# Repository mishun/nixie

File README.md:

Simple Nixe Clock
=================

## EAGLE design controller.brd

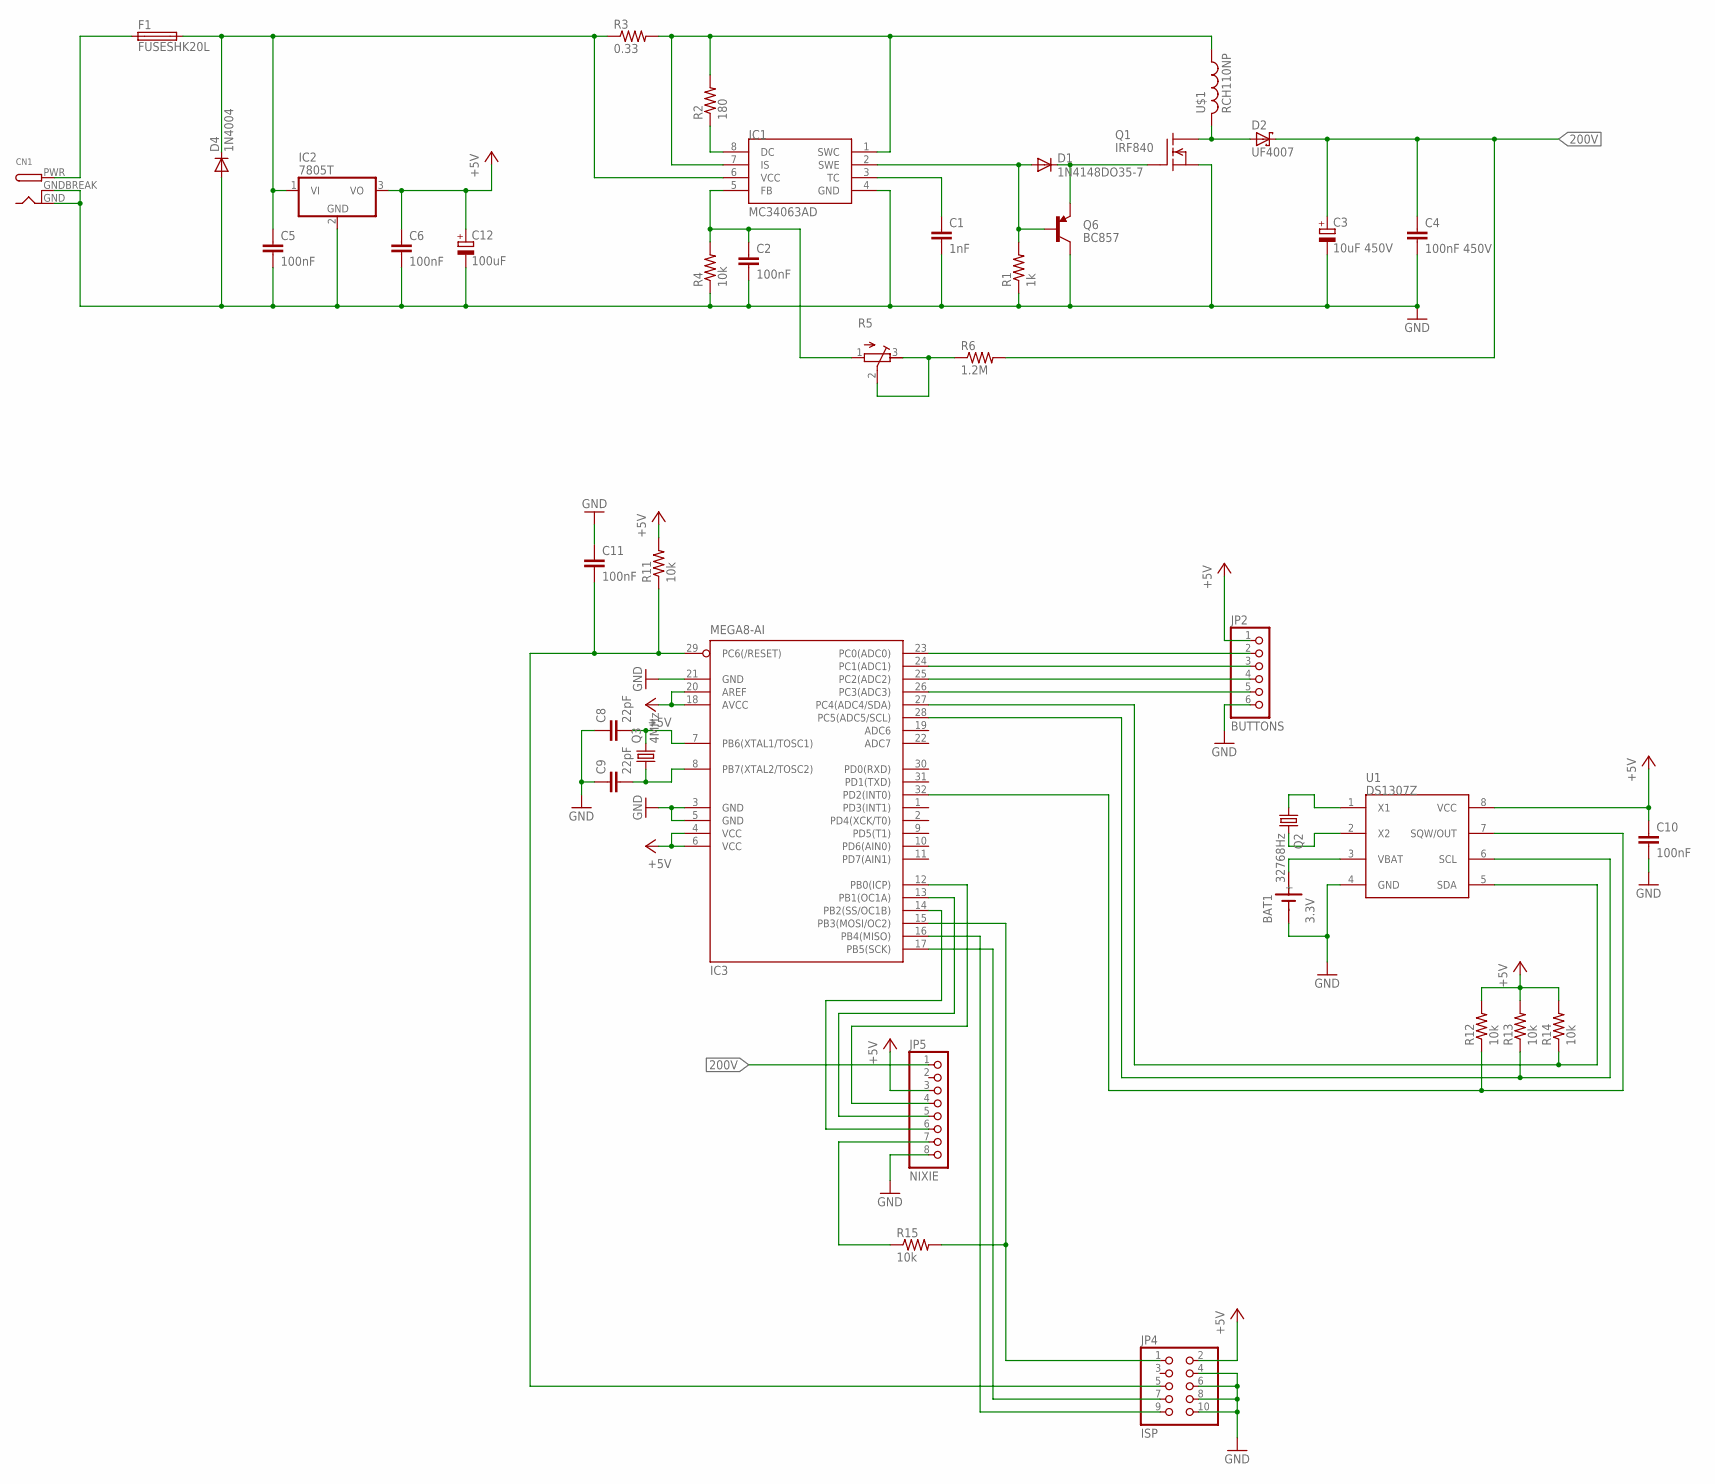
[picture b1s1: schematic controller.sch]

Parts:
BAT1: 3.3V; SN2032
C1: 1nF; 0805
C2, C5, C6, C10, C11: 100nF; 0805
C3: 10uF 450V; E5-13
C4: 100nF 450V; CAP-PTH-LARGE
C8, C9: 22pF; 0805
C12: 100uF; E3,5-8
CN1: DCBARRELPTH; DCJACK_2MM_PTH
D1: 1N4148DO35-7; DO35-7
D2: UF4007; DO41-7.6
D4: 1N4004; DO41-10
F1: FUSESHK20L; SHK20L
IC1: MC34063AD; SOIC8
IC2: 7805T; TO220H
IC3: MEGA8-AI; TQFP32-08
JP2: BUTTONS; 1X06/90
JP4: ISP; 2X05/90
JP5: NIXIE; 1X08
Q1: IRF840; TO220
Q2: 32768Hz; TC38H
Q3: 4MHz; HC49U-V
Q6: BC857; SOT23-3
R1: 1k; 0805
R2: 180; 0805
R3: 0.33; AXIAL-0.8
R4, R11, R12, R13, R14, R15: 10k; 0805
R5: R-TRIMM64Z; RTRIM64Z
R6: 1.2M; AXIAL-0.8
U1: DS1307Z; SOIC8
U$1: RCH110NP

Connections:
200V: C3.+, C4.1, D2.C, JP5.1, R6.P$2 (2)
+5V: C6.1, C10.1, C12.+, IC2.3 (VO), IC3.4 (VCC), IC3.6 (VCC), IC3.18 (AVCC), IC3.20 (AREF), JP2.1, JP4.2, JP5.3, R11.2, R12.2, R13.2, R14.2, U1.8 (VCC)
GND: BAT1.-, C1.2, C2.2, C3.-, C4.2, C5.2, C6.2, C8.1, C9.1, C10.2, C11.1, C12.-, CN1.GND, CN1.GNDBREAK, D4.A, IC1.4 (GND), IC2.2 (GND), IC3.3 (GND), IC3.5 (GND), IC3.21 (GND), JP2.6, JP4.4, JP4.6, JP4.8, JP4.10, JP5.8, Q1.3 (S), Q6.3 (C), R1.1, R4.1, U1.4 (GND)
unnamed: D1.C, Q1.1 (G), Q6.2 (E)
unnamed: D1.A, IC1.2 (SWE), Q6.1 (B), R1.2
unnamed: IC3.23 (PC0(ADC0)), JP2.2
unnamed: D2.A, Q1.2 (D), U$1.B (2)
unnamed: C1.1, IC1.3 (TC)
unnamed: IC1.8 (DC), R2.1
unnamed: IC1.1 (SWC), IC1.7 (IS), R2.2, R3.P$2 (2), U$1.A (1)
unnamed: C5.1, D4.C, F1.2A (2), IC1.6 (VCC), IC2.1 (VI), R3.P$1 (1)
unnamed: C11.2, IC3.29 (PC6(/RESET)), JP4.5, R11.1
unnamed: C2.1, IC1.5 (FB), R4.2, R5.1 (A)
unnamed: R5.2 (S), R5.3 (E), R6.P$1 (1)
unnamed: IC3.27 (PC4(ADC4/SDA)), R14.1, U1.5 (SDA)
unnamed: IC3.24 (PC1(ADC1)), JP2.3
unnamed: IC3.25 (PC2(ADC2)), JP2.4
unnamed: IC3.26 (PC3(ADC3)), JP2.5
unnamed: IC3.28 (PC5(ADC5/SCL)), R13.1, U1.6 (SCL)
unnamed: IC3.32 (PD2(INT0)), R12.1, U1.7 (SQW/OUT)
unnamed: IC3.15 (PB3(MOSI/OC2)), JP4.1, R15.2
unnamed: IC3.17 (PB5(SCK)), JP4.7
unnamed: IC3.16 (PB4(MISO)), JP4.9
unnamed: BAT1.+, U1.3 (VBAT)
unnamed: IC3.12 (PB0(ICP)), JP5.4
unnamed: Q2.1, U1.1 (X1)
unnamed: Q2.2, U1.2 (X2)
unnamed: C8.2, IC3.7 (PB6(XTAL1/TOSC1)), Q3.2
unnamed: C9.2, IC3.8 (PB7(XTAL2/TOSC2)), Q3.1
unnamed: CN1.PWR, F1.1A (1)
unnamed: IC3.13 (PB1(OC1A)), JP5.5
unnamed: IC3.14 (PB2(SS/OC1B)), JP5.6
unnamed: JP5.7, R15.1

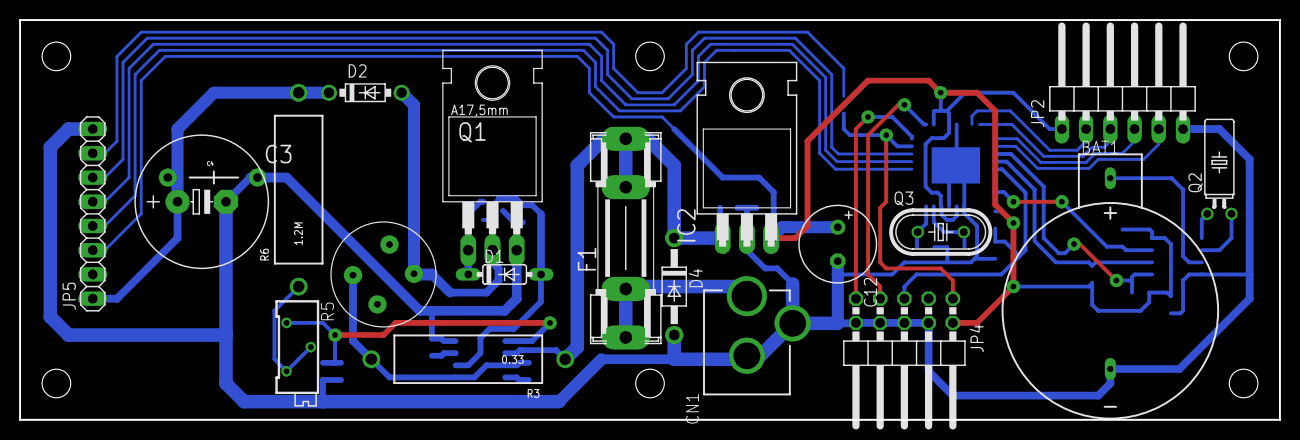
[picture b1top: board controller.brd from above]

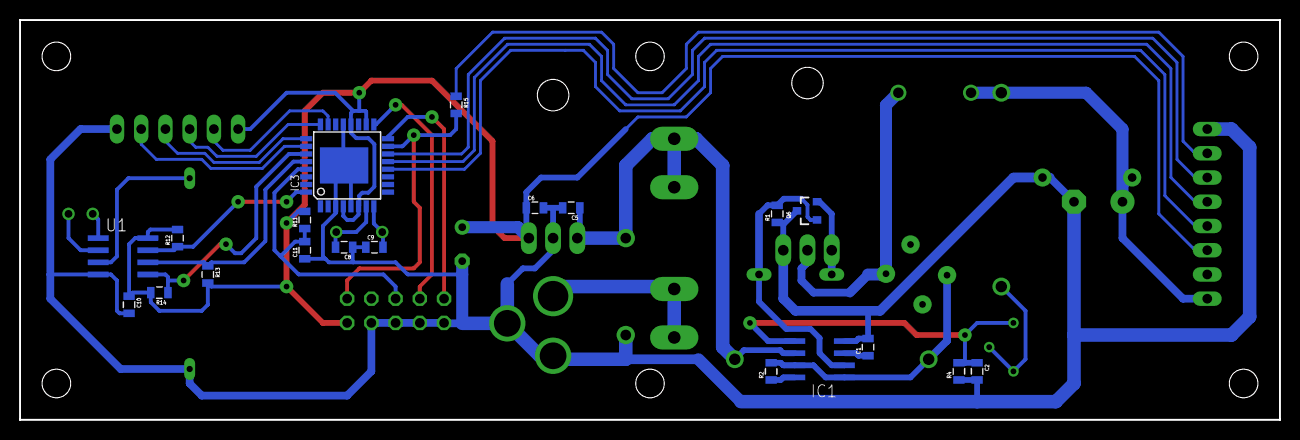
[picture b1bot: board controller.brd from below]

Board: 2 copper layers, 132.1 x 41.9 mm, 40 parts (20 on the bottom side), 33 nets.

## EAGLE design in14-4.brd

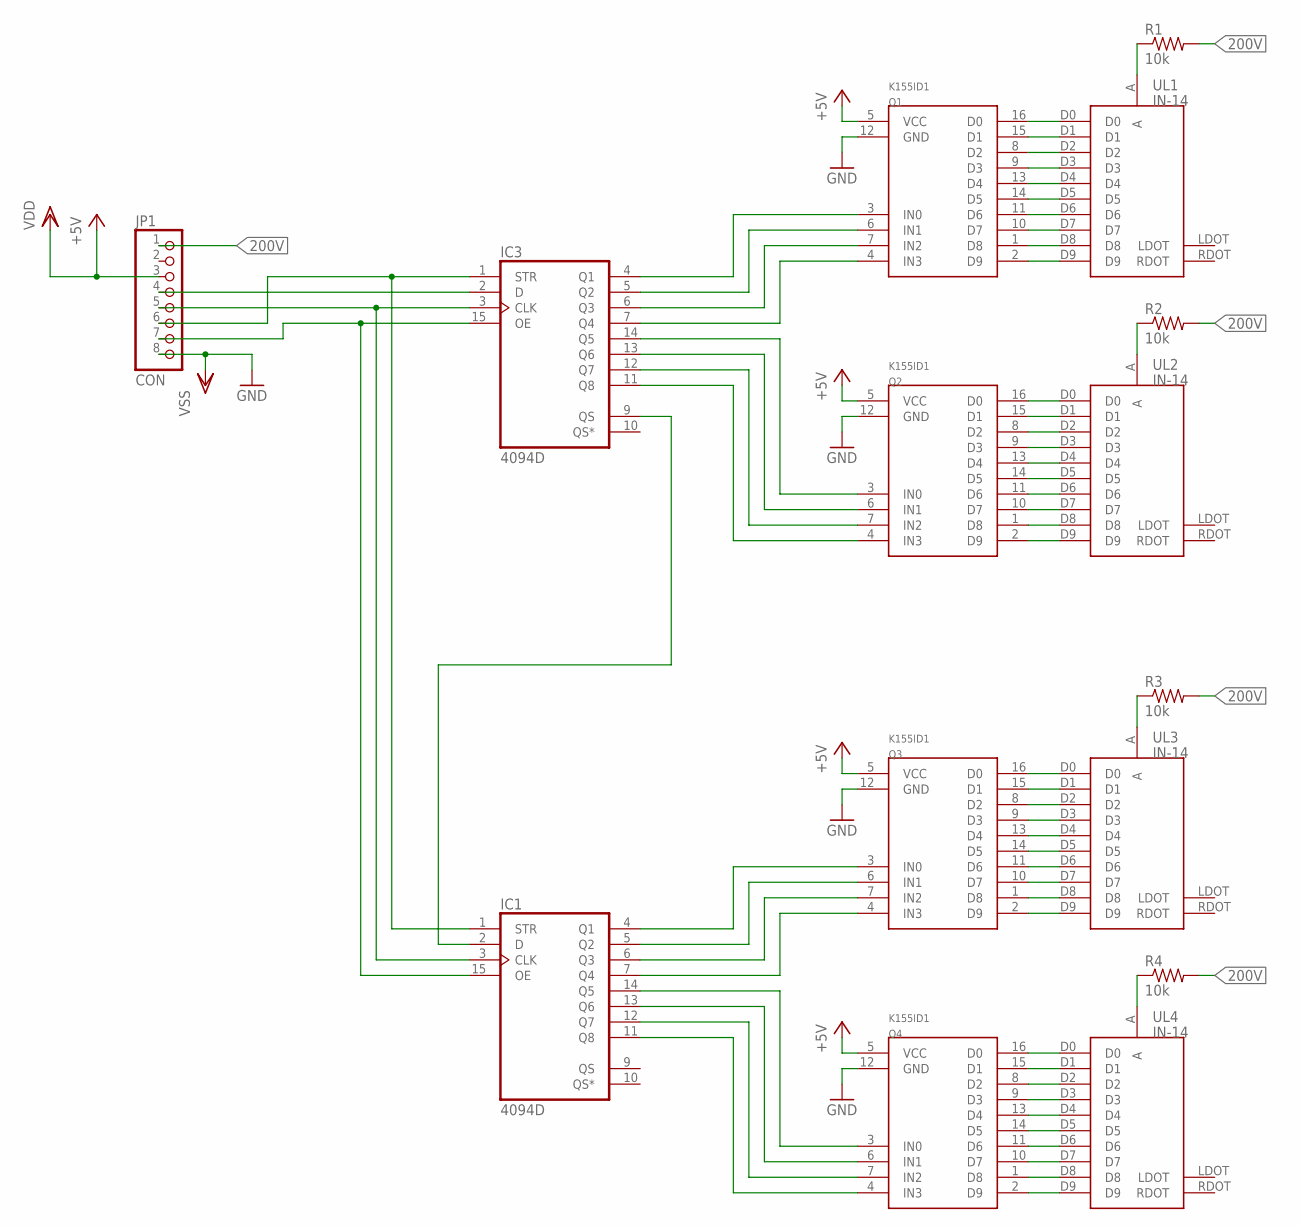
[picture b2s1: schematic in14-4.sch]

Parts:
IC1, IC3: 4094D; SO16
JP1: CON; 1X08
Q1, Q2, Q3, Q4: K155ID1; DIL16
R1, R2, R3, R4: 10k; 1206
UL1, UL2, UL3, UL4: IN-14

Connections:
200V: JP1.1, R1.2, R2.2, R3.2, R4.2
+5V: IC1.16 (VDD), IC3.16 (VDD), JP1.3, Q1.5 (VCC), Q2.5 (VCC), Q3.5 (VCC), Q4.5 (VCC)
GND: IC1.8 (VSS), IC3.8 (VSS), JP1.8, Q1.12 (GND), Q2.12 (GND), Q3.12 (GND), Q4.12 (GND)
unnamed: Q1.16 (D0), UL1.D0
unnamed: Q1.15 (D1), UL1.D1
unnamed: Q1.8 (D2), UL1.D2
unnamed: Q1.9 (D3), UL1.D3
unnamed: Q1.13 (D4), UL1.D4
unnamed: Q1.14 (D5), UL1.D5
unnamed: Q1.11 (D6), UL1.D6
unnamed: Q1.10 (D7), UL1.D7
unnamed: Q1.1 (D8), UL1.D8
unnamed: Q1.2 (D9), UL1.D9
unnamed: R1.1, UL1.A
unnamed: Q2.16 (D0), UL2.D0
unnamed: Q2.15 (D1), UL2.D1
unnamed: Q2.8 (D2), UL2.D2
unnamed: Q2.9 (D3), UL2.D3
unnamed: Q2.13 (D4), UL2.D4
unnamed: Q2.14 (D5), UL2.D5
unnamed: Q2.11 (D6), UL2.D6
unnamed: Q2.10 (D7), UL2.D7
unnamed: Q2.1 (D8), UL2.D8
unnamed: Q2.2 (D9), UL2.D9
unnamed: R2.1, UL2.A
unnamed: Q3.2 (D9), UL3.D9
unnamed: IC3.5 (Q2), Q1.6 (IN1)
unnamed: Q3.11 (D6), UL3.D6
unnamed: IC3.13 (Q6), Q2.6 (IN1)
unnamed: IC3.12 (Q7), Q2.7 (IN2)
unnamed: IC3.11 (Q8), Q2.4 (IN3)
unnamed: IC3.2 (D), JP1.4
unnamed: IC1.3 (CLK), IC3.3 (CLK), JP1.5
unnamed: IC1.1 (STR), IC3.1 (STR), JP1.6
unnamed: IC1.15 (OE), IC3.15 (OE), JP1.7
unnamed: IC1.7 (Q4), Q3.4 (IN3)
unnamed: IC1.6 (Q3), Q3.7 (IN2)
unnamed: IC1.5 (Q2), Q3.6 (IN1)
unnamed: IC1.4 (Q1), Q3.3 (IN0)
unnamed: IC1.14 (Q5), Q4.3 (IN0)
unnamed: IC1.13 (Q6), Q4.6 (IN1)
unnamed: IC1.12 (Q7), Q4.7 (IN2)
unnamed: IC1.11 (Q8), Q4.4 (IN3)
unnamed: Q3.16 (D0), UL3.D0
unnamed: Q3.15 (D1), UL3.D1
unnamed: Q3.8 (D2), UL3.D2
unnamed: Q3.9 (D3), UL3.D3
unnamed: Q3.13 (D4), UL3.D4
unnamed: Q3.14 (D5), UL3.D5
unnamed: Q3.10 (D7), UL3.D7
unnamed: Q3.1 (D8), UL3.D8
unnamed: Q4.16 (D0), UL4.D0
unnamed: Q4.15 (D1), UL4.D1
unnamed: Q4.8 (D2), UL4.D2
unnamed: Q4.9 (D3), UL4.D3
unnamed: Q4.13 (D4), UL4.D4
unnamed: Q4.14 (D5), UL4.D5
unnamed: Q4.11 (D6), UL4.D6
unnamed: Q4.10 (D7), UL4.D7
unnamed: Q4.1 (D8), UL4.D8
unnamed: Q4.2 (D9), UL4.D9
unnamed: IC3.4 (Q1), Q1.3 (IN0)
unnamed: R3.1, UL3.A
unnamed: R4.1, UL4.A
unnamed: IC1.2 (D), IC3.9 (QS)
unnamed: IC3.7 (Q4), Q1.4 (IN3)
unnamed: IC3.6 (Q3), Q1.7 (IN2)
unnamed: IC3.14 (Q5), Q2.3 (IN0)

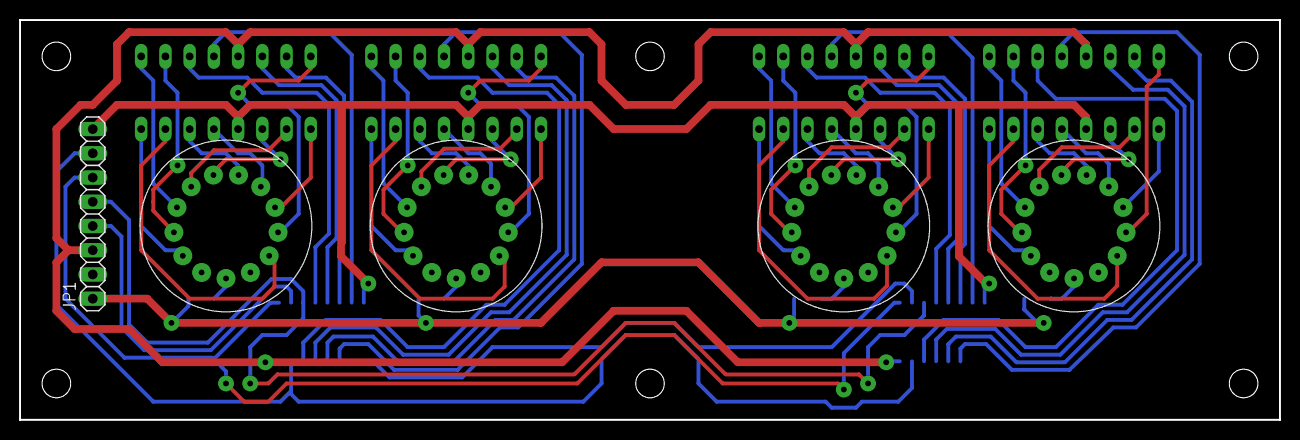
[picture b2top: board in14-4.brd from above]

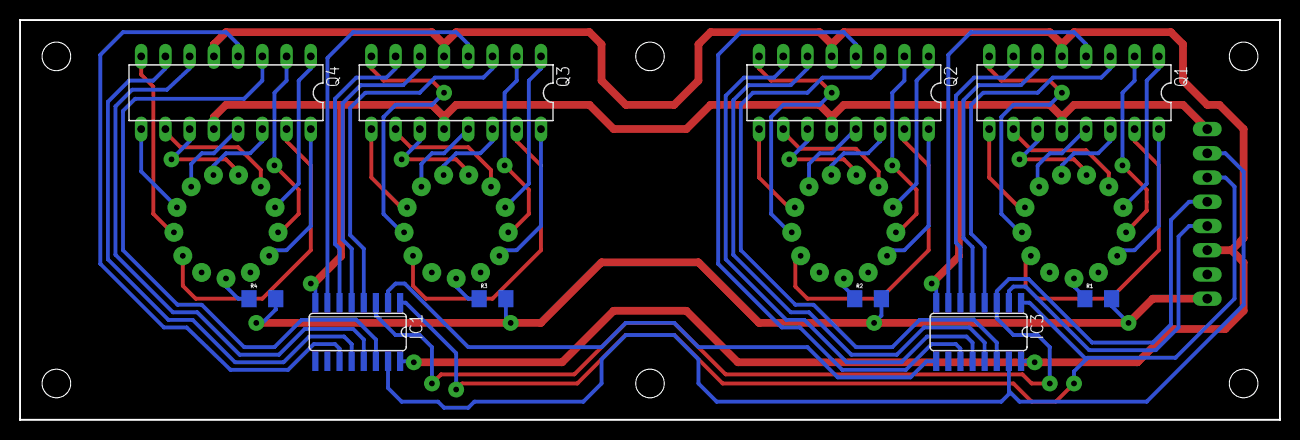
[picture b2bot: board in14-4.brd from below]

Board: 2 copper layers, 132.1 x 41.9 mm, 15 parts (10 on the bottom side), 68 nets.

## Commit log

2012-08-26 Existing files added
2012-08-31 Finishing extra components
2012-08-31 Library with custom components added
2012-09-14 Fixing ERC errors
2012-09-15 Dimensions defined
2013-03-26 gitignore added
2013-08-17 IN-14 layers fix
2013-08-27 Controller
2013-09-13 Controller prototype finished
2013-10-01 Todo list added
2013-10-01 Firmware started
2013-10-02 Async I2C + Watchdog
2013-10-02 PWM brightness control
2013-10-02 Possible race condition in I2C fix
2013-10-02 Sensor buttons implementation started + date and time routines
2013-10-05 Correct pnp transistor pinout

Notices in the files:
parts and their libraries:
SparkFun-Passives: Licensing: CC v3.0 Share-Alike You are welcome to use this library for commercial purposes.
